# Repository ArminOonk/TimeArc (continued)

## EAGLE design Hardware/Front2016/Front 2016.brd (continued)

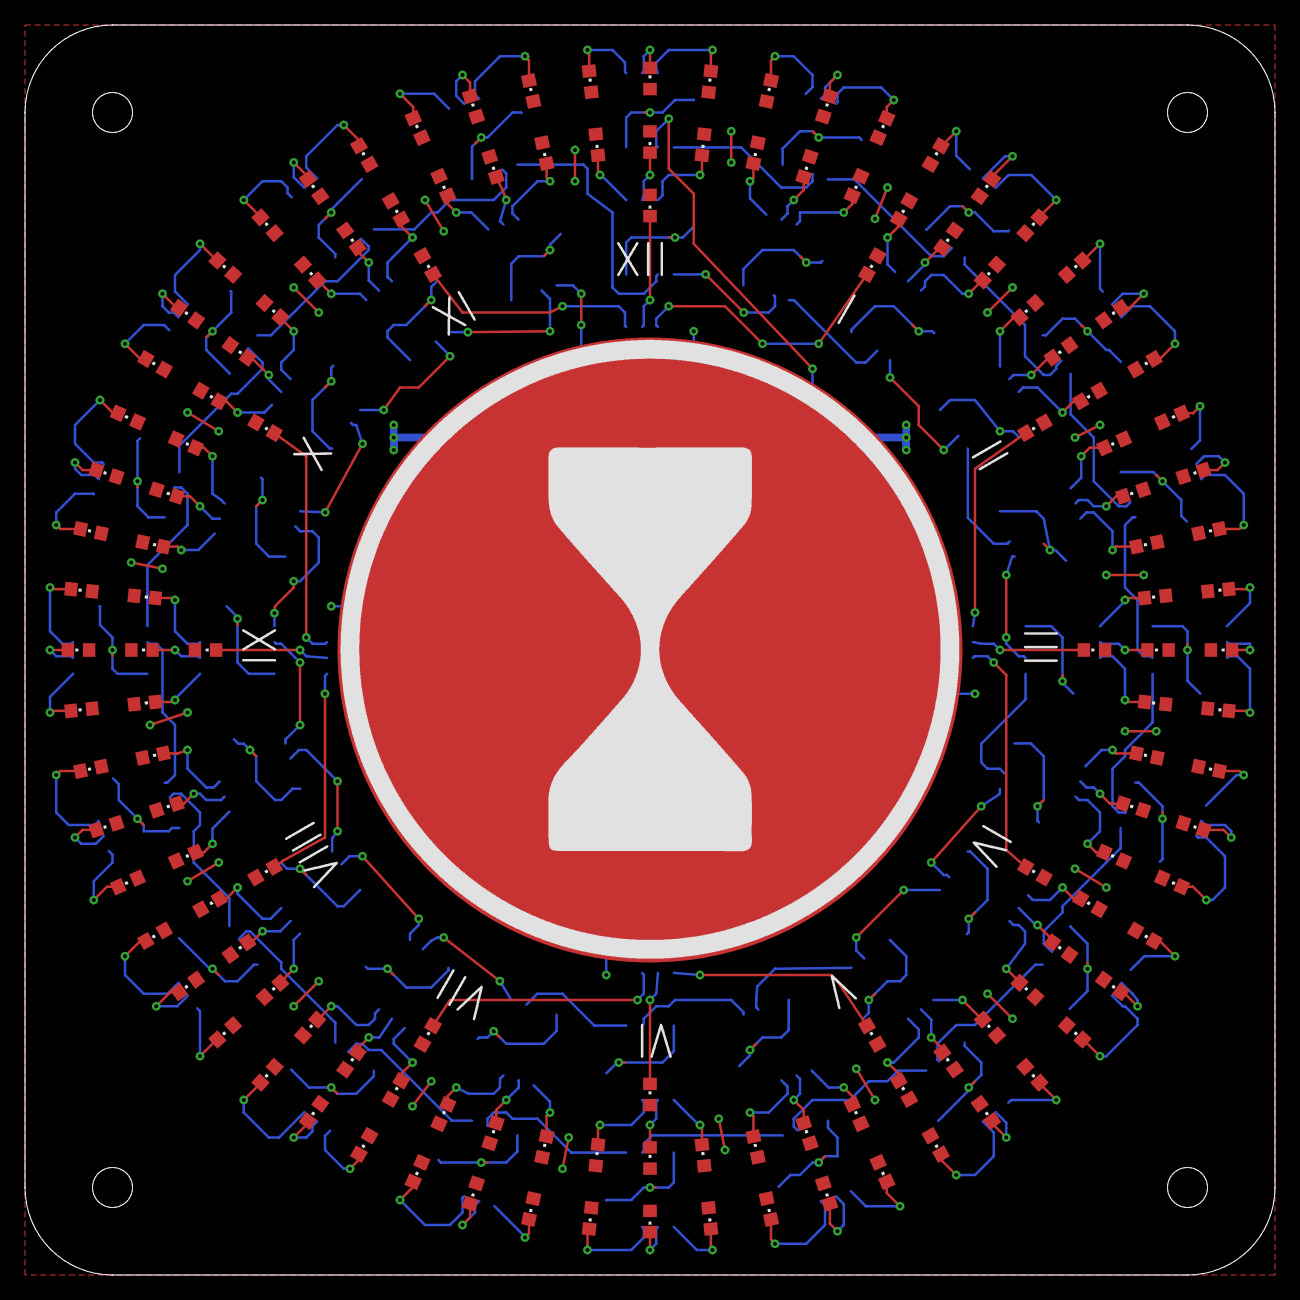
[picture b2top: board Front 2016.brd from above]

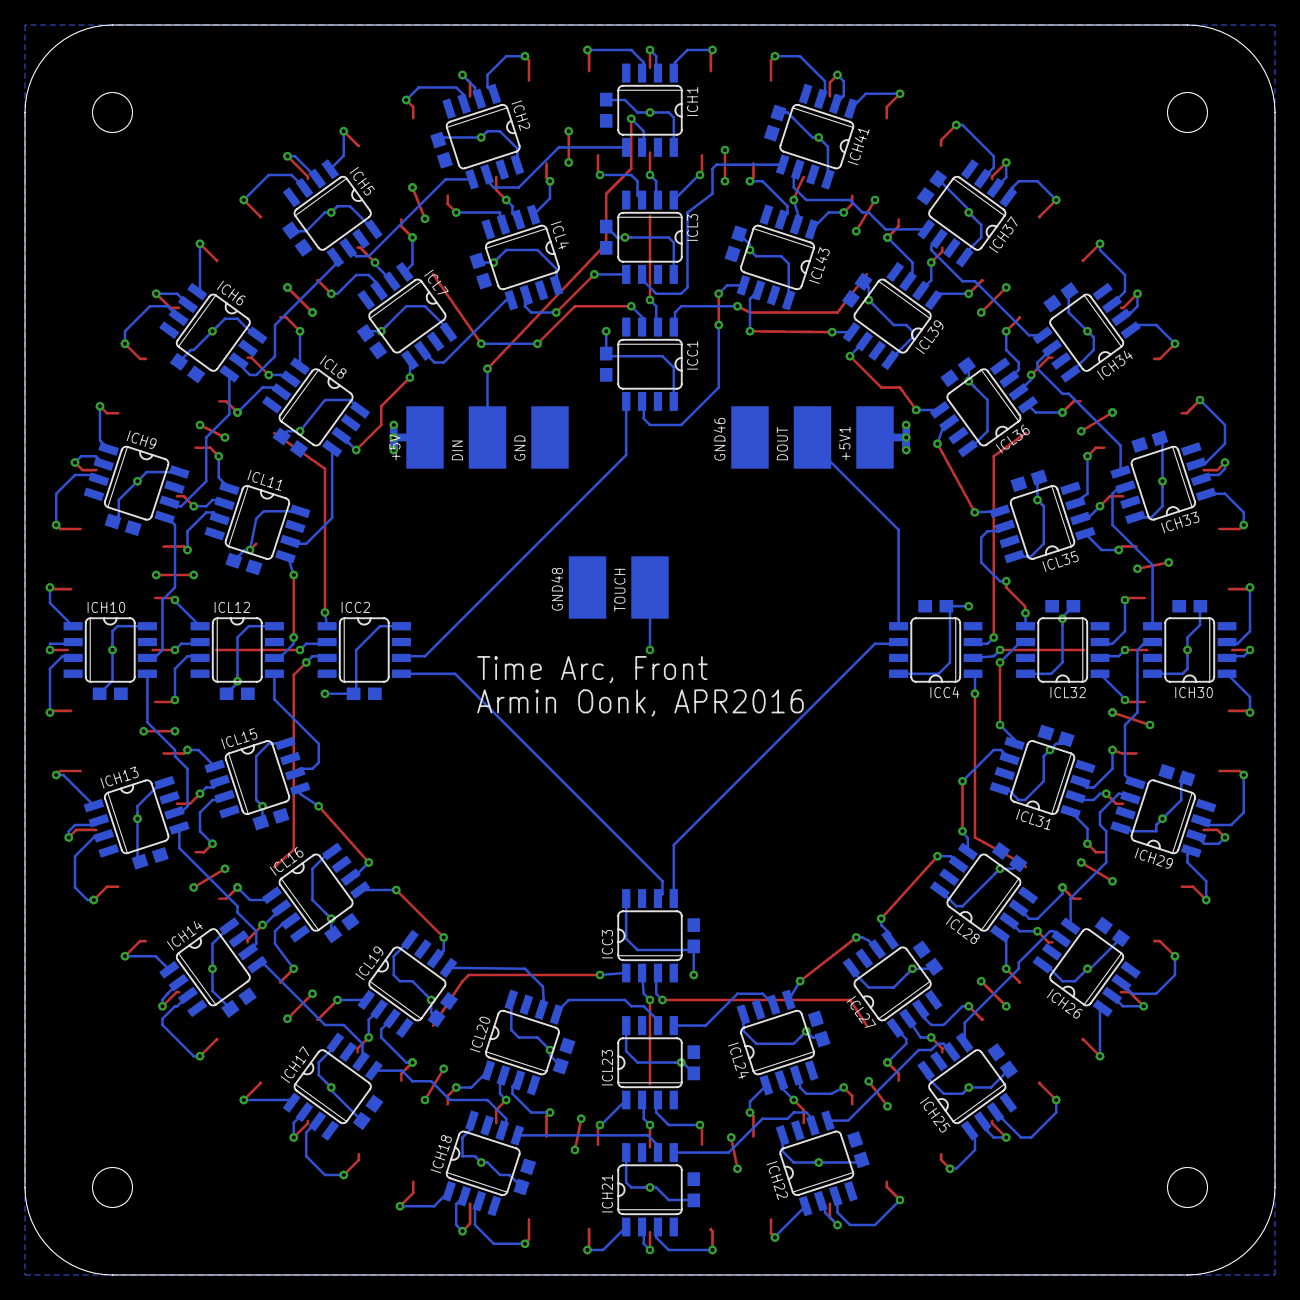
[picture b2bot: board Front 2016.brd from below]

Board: 2 copper layers, 100.0 x 100.0 mm, 187 parts (52 on the bottom side), 180 nets.

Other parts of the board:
U$1: TIMEARC_KEEPOUT
U$3: TIMEARC_LOGO_SIMPLE

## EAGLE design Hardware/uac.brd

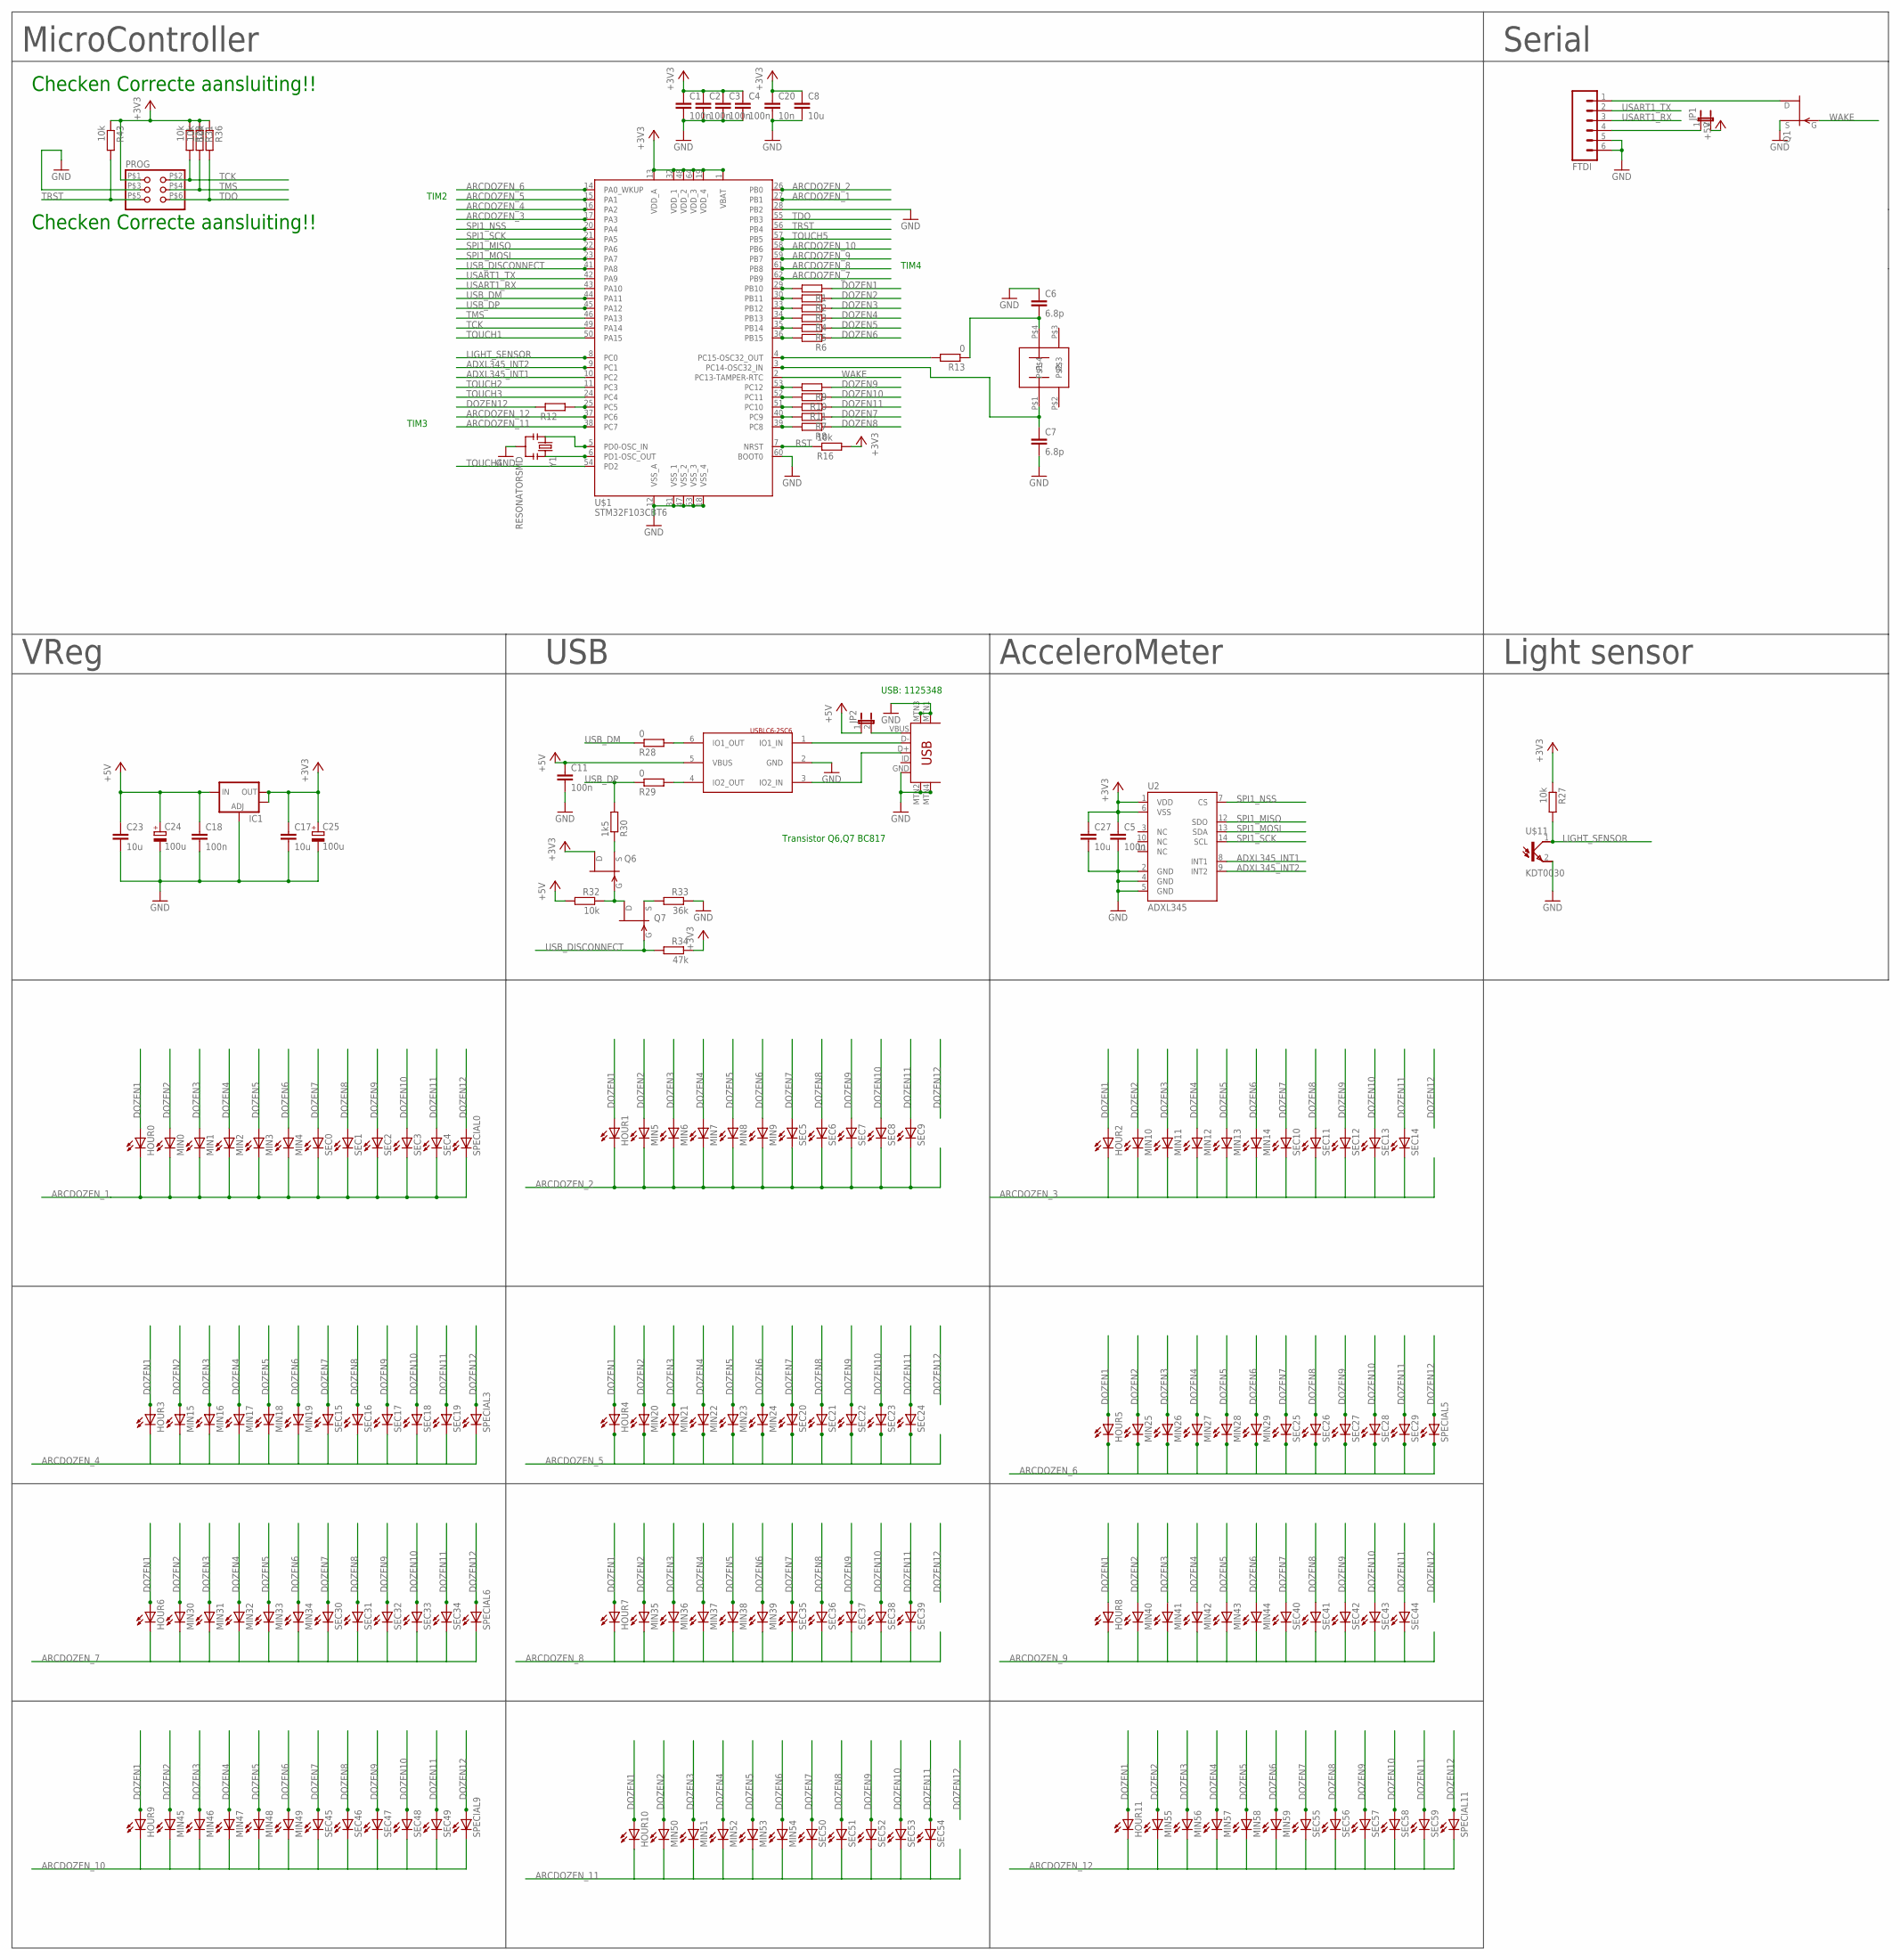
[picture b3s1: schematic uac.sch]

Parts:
C1, C2, C3, C4, C5, C11, C18: 100n; C0603
C6, C7: 6.8p; C0603
C8, C17, C23, C27: 10u; C0603
C20: 10n; C0603
C24, C25: 100u; SMC_C
FTDI: M06SMD; 1X06-SMD
HOUR0, HOUR1, HOUR2, HOUR3, HOUR4, HOUR5, HOUR6, HOUR7, HOUR8, HOUR9, HOUR10, HOUR11: LEDCHIPLED_0603; CHIPLED_0603
IC1: V_REG_LM1117SOT223; SOT223
JP1, JP2: JUMPER-2SMD-NO; SJ_2S-NO
MIN0, MIN1, MIN2, MIN3, MIN4, MIN5, MIN6, MIN7, MIN8, MIN9, MIN10, MIN11, MIN12, MIN13, MIN14, MIN15, MIN16, MIN17, MIN18, MIN19, MIN20, MIN21, MIN22, MIN23, MIN24, MIN25, MIN26, MIN27, MIN28, MIN29, MIN30, MIN31, MIN32, MIN33, MIN34, MIN35, MIN36, MIN37, MIN38, MIN39, MIN40, MIN41, MIN42, MIN43, MIN44, MIN45, MIN46, MIN47, MIN48, MIN49, MIN50, MIN51, MIN52, MIN53, MIN54, MIN55, MIN56, MIN57, MIN58, MIN59: LEDCHIPLED_0603; CHIPLED_0603
PROG: PINHD-2X3SMT; 2X03_SMT
Q1, Q6, Q7: 2N7002CK4SST; SOT23
R1, R2, R3, R4, R5, R6, R7, R8, R9, R10, R11, R12: R-EU_R0603; R0603
R13, R28, R29: 0; R0603
R16, R23, R27, R31, R32, R36, R43: 10k; R0603
R30: 1k5; R0603
R33: 36k; R0603
R34: 47k; R0603
SEC0, SEC1, SEC2, SEC3, SEC4, SEC5, SEC6, SEC7, SEC8, SEC9, SEC10, SEC11, SEC12, SEC13, SEC14, SEC15, SEC16, SEC17, SEC18, SEC19, SEC20, SEC21, SEC22, SEC23, SEC24, SEC25, SEC26, SEC27, SEC28, SEC29, SEC30, SEC31, SEC32, SEC33, SEC34, SEC35, SEC36, SEC37, SEC38, SEC39, SEC40, SEC41, SEC42, SEC43, SEC44, SEC45, SEC46, SEC47, SEC48, SEC49, SEC50, SEC51, SEC52, SEC53, SEC54, SEC55, SEC56, SEC57, SEC58, SEC59: LEDCHIPLED_0603; CHIPLED_0603
SPECIAL0, SPECIAL3, SPECIAL5, SPECIAL6, SPECIAL9, SPECIAL11: LEDCHIPLED_0603; CHIPLED_0603
U2: ADXL345; LGA14
U$1: STM32F103CBT6; LQFP64
U$2: CRYSTAL_32KHZ
U$11: KDT0030; FLD00030
U$12: USB-MINIB-5PIN; USB-MINIB
U$13: USBLC6-2SC6; SOT23
Y1: RESONATORSMD; RESONATOR-SMD

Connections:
+3V3: C1.1, C2.1, C3.1, C4.1, C5.1, C8.1, C17.1, C20.1, C25.+, C27.1, IC1.2 (OUT), IC1.4 (OUT), PROG.P$1 (1), Q6.3 (D), R16.2, R23.1, R27.1, R31.1, R34.1, R36.1, R43.1, U2.1 (VDD), U2.6 (VSS), U$1.1 (VBAT), U$1.13 (VDD_A), U$1.19 (VDD_4), U$1.32 (VDD_1), U$1.48 (VDD_2), U$1.64 (VDD_3)
+5V: C11.1, C18.1, C23.1, C24.+, IC1.3 (IN), JP1.2, JP2.1, R32.2, U$13.5 (VBUS)
ADXL345_INT1: U2.8 (INT1), U$1.10 (PC2)
ADXL345_INT2: U2.9 (INT2), U$1.9 (PC1)
ARCDOZEN_1: HOUR0.C, MIN0.C, MIN1.C, MIN2.C, MIN3.C, MIN4.C, SEC0.C, SEC1.C, SEC2.C, SEC3.C, SEC4.C, SPECIAL0.C, U$1.27 (PB1)
ARCDOZEN_2: HOUR1.C, MIN5.C, MIN6.C, MIN7.C, MIN8.C, MIN9.C, SEC5.C, SEC6.C, SEC7.C, SEC8.C, SEC9.C, U$1.26 (PB0)
ARCDOZEN_3: HOUR2.C, MIN10.C, MIN11.C, MIN12.C, MIN13.C, MIN14.C, SEC10.C, SEC11.C, SEC12.C, SEC13.C, SEC14.C, U$1.17 (PA3)
ARCDOZEN_4: HOUR3.C, MIN15.C, MIN16.C, MIN17.C, MIN18.C, MIN19.C, SEC15.C, SEC16.C, SEC17.C, SEC18.C, SEC19.C, SPECIAL3.C, U$1.16 (PA2)
ARCDOZEN_5: HOUR4.C, MIN20.C, MIN21.C, MIN22.C, MIN23.C, MIN24.C, SEC20.C, SEC21.C, SEC22.C, SEC23.C, SEC24.C, U$1.15 (PA1)
ARCDOZEN_6: HOUR5.C, MIN25.C, MIN26.C, MIN27.C, MIN28.C, MIN29.C, SEC25.C, SEC26.C, SEC27.C, SEC28.C, SEC29.C, SPECIAL5.C, U$1.14 (PA0_WKUP)
ARCDOZEN_7: HOUR6.C, MIN30.C, MIN31.C, MIN32.C, MIN33.C, MIN34.C, SEC30.C, SEC31.C, SEC32.C, SEC33.C, SEC34.C, SPECIAL6.C, U$1.62 (PB9)
ARCDOZEN_8: HOUR7.C, MIN35.C, MIN36.C, MIN37.C, MIN38.C, MIN39.C, SEC35.C, SEC36.C, SEC37.C, SEC38.C, SEC39.C, U$1.61 (PB8)
ARCDOZEN_9: HOUR8.C, MIN40.C, MIN41.C, MIN42.C, MIN43.C, MIN44.C, SEC40.C, SEC41.C, SEC42.C, SEC43.C, SEC44.C, U$1.59 (PB7)
ARCDOZEN_10: HOUR9.C, MIN45.C, MIN46.C, MIN47.C, MIN48.C, MIN49.C, SEC45.C, SEC46.C, SEC47.C, SEC48.C, SEC49.C, SPECIAL9.C, U$1.58 (PB6)
ARCDOZEN_11: HOUR10.C, MIN50.C, MIN51.C, MIN52.C, MIN53.C, MIN54.C, SEC50.C, SEC51.C, SEC52.C, SEC53.C, SEC54.C, U$1.38 (PC7)
ARCDOZEN_12: HOUR11.C, MIN55.C, MIN56.C, MIN57.C, MIN58.C, MIN59.C, SEC55.C, SEC56.C, SEC57.C, SEC58.C, SEC59.C, SPECIAL11.C, U$1.37 (PC6)
DOZEN1: HOUR0.A, HOUR1.A, HOUR2.A, HOUR3.A, HOUR4.A, HOUR5.A, HOUR6.A, HOUR7.A, HOUR8.A, HOUR9.A, HOUR10.A, HOUR11.A, R1.1
DOZEN2: MIN0.A, MIN5.A, MIN10.A, MIN15.A, MIN20.A, MIN25.A, MIN30.A, MIN35.A, MIN40.A, MIN45.A, MIN50.A, MIN55.A, R2.1
DOZEN3: MIN1.A, MIN6.A, MIN11.A, MIN16.A, MIN21.A, MIN26.A, MIN31.A, MIN36.A, MIN41.A, MIN46.A, MIN51.A, MIN56.A, R3.1
DOZEN4: MIN2.A, MIN7.A, MIN12.A, MIN17.A, MIN22.A, MIN27.A, MIN32.A, MIN37.A, MIN42.A, MIN47.A, MIN52.A, MIN57.A, R4.1
DOZEN5: MIN3.A, MIN8.A, MIN13.A, MIN18.A, MIN23.A, MIN28.A, MIN33.A, MIN38.A, MIN43.A, MIN48.A, MIN53.A, MIN58.A, R5.1
DOZEN6: MIN4.A, MIN9.A, MIN14.A, MIN19.A, MIN24.A, MIN29.A, MIN34.A, MIN39.A, MIN44.A, MIN49.A, MIN54.A, MIN59.A, R6.1
DOZEN7: R7.1, SEC0.A, SEC5.A, SEC10.A, SEC15.A, SEC20.A, SEC25.A, SEC30.A, SEC35.A, SEC40.A, SEC45.A, SEC50.A, SEC55.A
DOZEN8: R8.1, SEC1.A, SEC6.A, SEC11.A, SEC16.A, SEC21.A, SEC26.A, SEC31.A, SEC36.A, SEC41.A, SEC46.A, SEC51.A, SEC56.A
DOZEN9: R9.1, SEC2.A, SEC7.A, SEC12.A, SEC17.A, SEC22.A, SEC27.A, SEC32.A, SEC37.A, SEC42.A, SEC47.A, SEC52.A, SEC57.A
DOZEN10: R10.1, SEC3.A, SEC8.A, SEC13.A, SEC18.A, SEC23.A, SEC28.A, SEC33.A, SEC38.A, SEC43.A, SEC48.A, SEC53.A, SEC58.A
DOZEN11: R11.1, SEC4.A, SEC9.A, SEC14.A, SEC19.A, SEC24.A, SEC29.A, SEC34.A, SEC39.A, SEC44.A, SEC49.A, SEC54.A, SEC59.A
DOZEN12: R12.1, SPECIAL0.A, SPECIAL3.A, SPECIAL5.A, SPECIAL6.A, SPECIAL9.A, SPECIAL11.A
GND: C1.2, C2.2, C3.2, C4.2, C5.2, C6.1, C7.2, C8.2, C11.2, C17.2, C18.2, C20.2, C23.2, C24.-, C25.-, C27.2, FTDI.5, FTDI.6, IC1.1 (ADJ), PROG.P$3 (3), Q1.2 (S), R33.1, U2.2 (GND), U2.4 (GND), U2.5 (GND), U$1.12 (VSS_A), U$1.18 (VSS_4), U$1.28 (PB2), U$1.31 (VSS_1), U$1.47 (VSS_2), U$1.60 (BOOT0), U$1.63 (VSS_3), U$11.2 (EMI), U$12.GND, U$12.MTN1 (MTN2), U$12.MTN2 (MTN3), U$12.MTN3 (MTN1), U$12.MTN4, U$13.2 (GND), Y1.2
LIGHT_SENSOR: R27.2, U$1.8 (PC0), U$11.1 (COL)
unnamed: U$1.6 (PD1-OSC_OUT), Y1.3
unnamed: U$1.5 (PD0-OSC_IN), Y1.1
unnamed: JP2.2, U$12.VBUS
unnamed: R13.2, U$1.4 (PC15-OSC32_OUT)
unnamed: C6.2, R13.1, U$2.P$4
unnamed: C7.1, U$1.3 (PC14-OSC32_IN), U$2.P$1
unnamed: R1.2, U$1.29 (PB10)
unnamed: R2.2, U$1.30 (PB11)
unnamed: R3.2, U$1.33 (PB12)
unnamed: R4.2, U$1.34 (PB13)
unnamed: R5.2, U$1.35 (PB14)
unnamed: R6.2, U$1.36 (PB15)
unnamed: R7.2, U$1.40 (PC9)
unnamed: R8.2, U$1.39 (PC8)
unnamed: R9.2, U$1.53 (PC12)
unnamed: R10.2, U$1.52 (PC11)
unnamed: R11.2, U$1.51 (PC10)
unnamed: U$12.D-, U$13.1 (IO1_IN)
unnamed: FTDI.4, JP1.1
unnamed: FTDI.1, Q1.3 (D)
unnamed: U$12.D+, U$13.3 (IO2_IN)
unnamed: R12.2, U$1.25 (PC5)
unnamed: R28.2, U$13.6 (IO1_OUT)
unnamed: R29.2, U$13.4 (IO2_OUT)
unnamed: Q6.2 (S), R30.1
unnamed: Q6.1 (G), Q7.3 (D), R32.1
unnamed: Q7.2 (S), R33.2
RST: R16.1, U$1.7 (NRST)
SPI1_MISO: U2.12 (SDO), U$1.22 (PA6)
SPI1_MOSI: U2.13 (SDA), U$1.23 (PA7)
SPI1_NSS: U2.7 (CS), U$1.20 (PA4)
SPI1_SCK: U2.14 (SCL), U$1.21 (PA5)
TCK: PROG.P$2 (2), R23.2, U$1.49 (PA14)
TDO: PROG.P$6 (6), R36.2, U$1.55 (PB3)
TMS: PROG.P$4 (4), R31.2, U$1.46 (PA13)
TOUCH1: U$1.50 (PA15)
TOUCH2: U$1.11 (PC3)
TOUCH3: U$1.24 (PC4)
TOUCH4: U$1.54 (PD2)
TOUCH5: U$1.57 (PB5)
TRST: PROG.P$5 (5), R43.2, U$1.56 (PB4)
USART1_RX: FTDI.3, U$1.43 (PA10)
USART1_TX: FTDI.2, U$1.42 (PA9)
USB_DISCONNECT: Q7.1 (G), R34.2, U$1.41 (PA8)
USB_DM: R28.1, U$1.44 (PA11)
USB_DP: R29.1, R30.2, U$1.45 (PA12)
WAKE: Q1.1 (G), U$1.2 (PC13-TAMPER-RTC)

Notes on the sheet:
Checken Correcte aansluiting!!
TIM2
TIM4
VReg
MicroController
AcceleroMeter
Light sensor
Serial
USB
USB: 1125348
Transistor Q6,Q7 BC817
TIM3

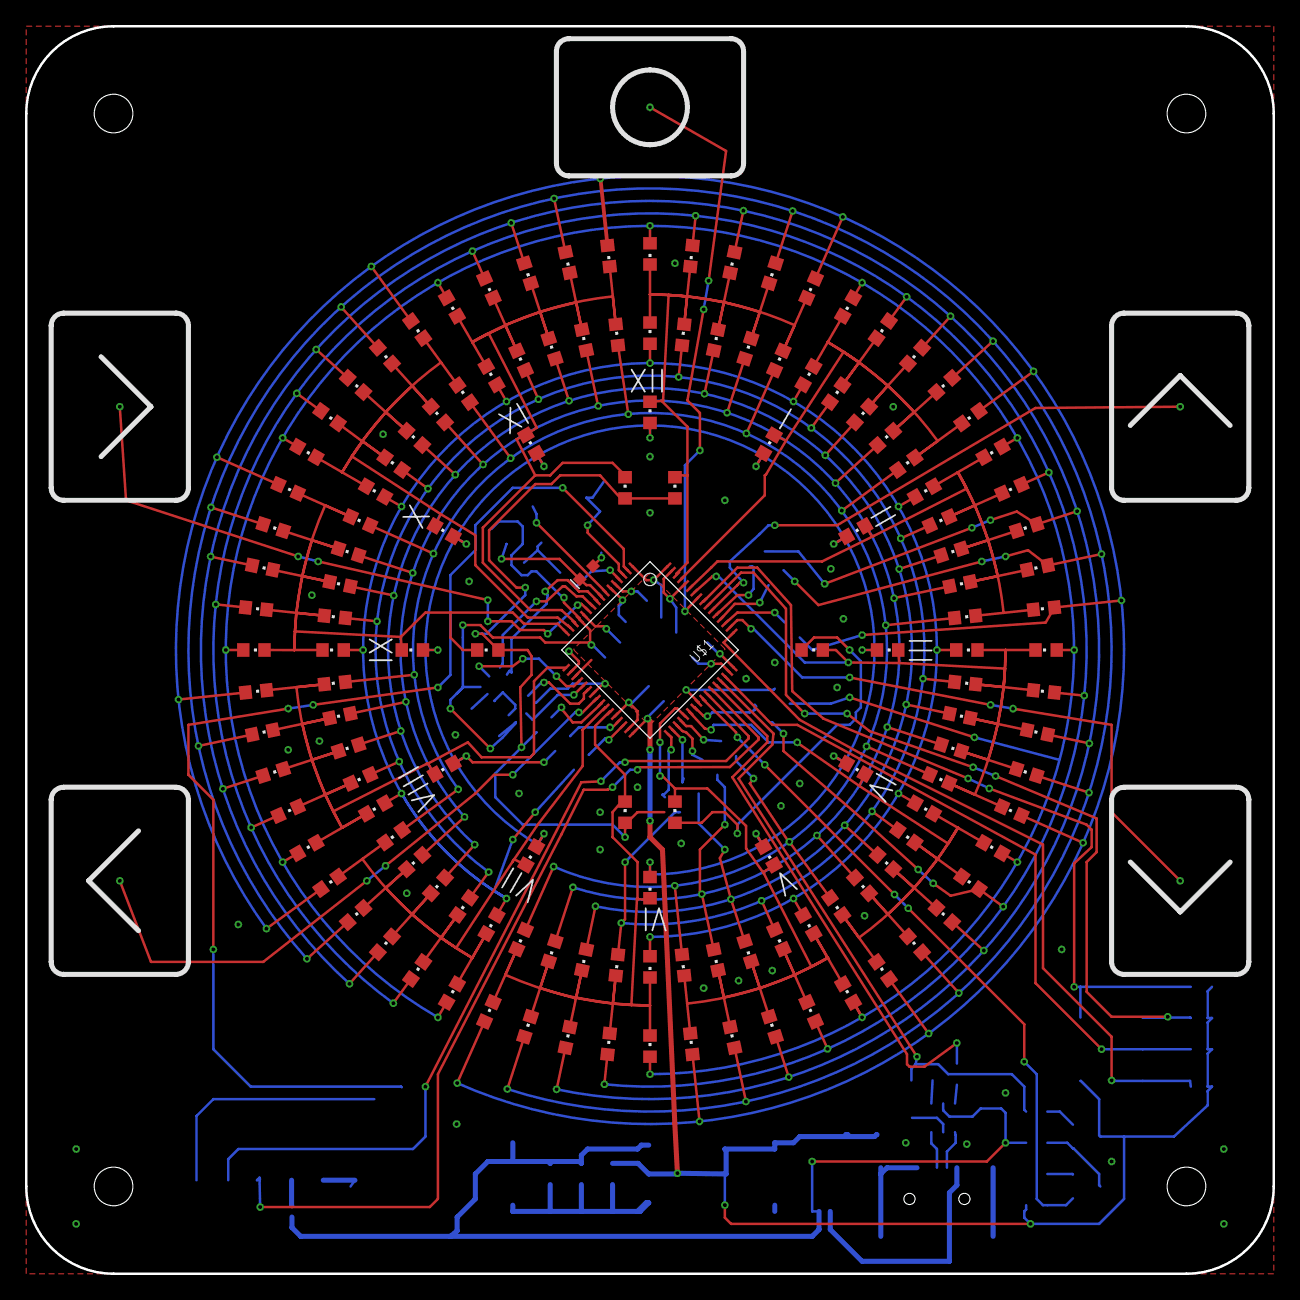
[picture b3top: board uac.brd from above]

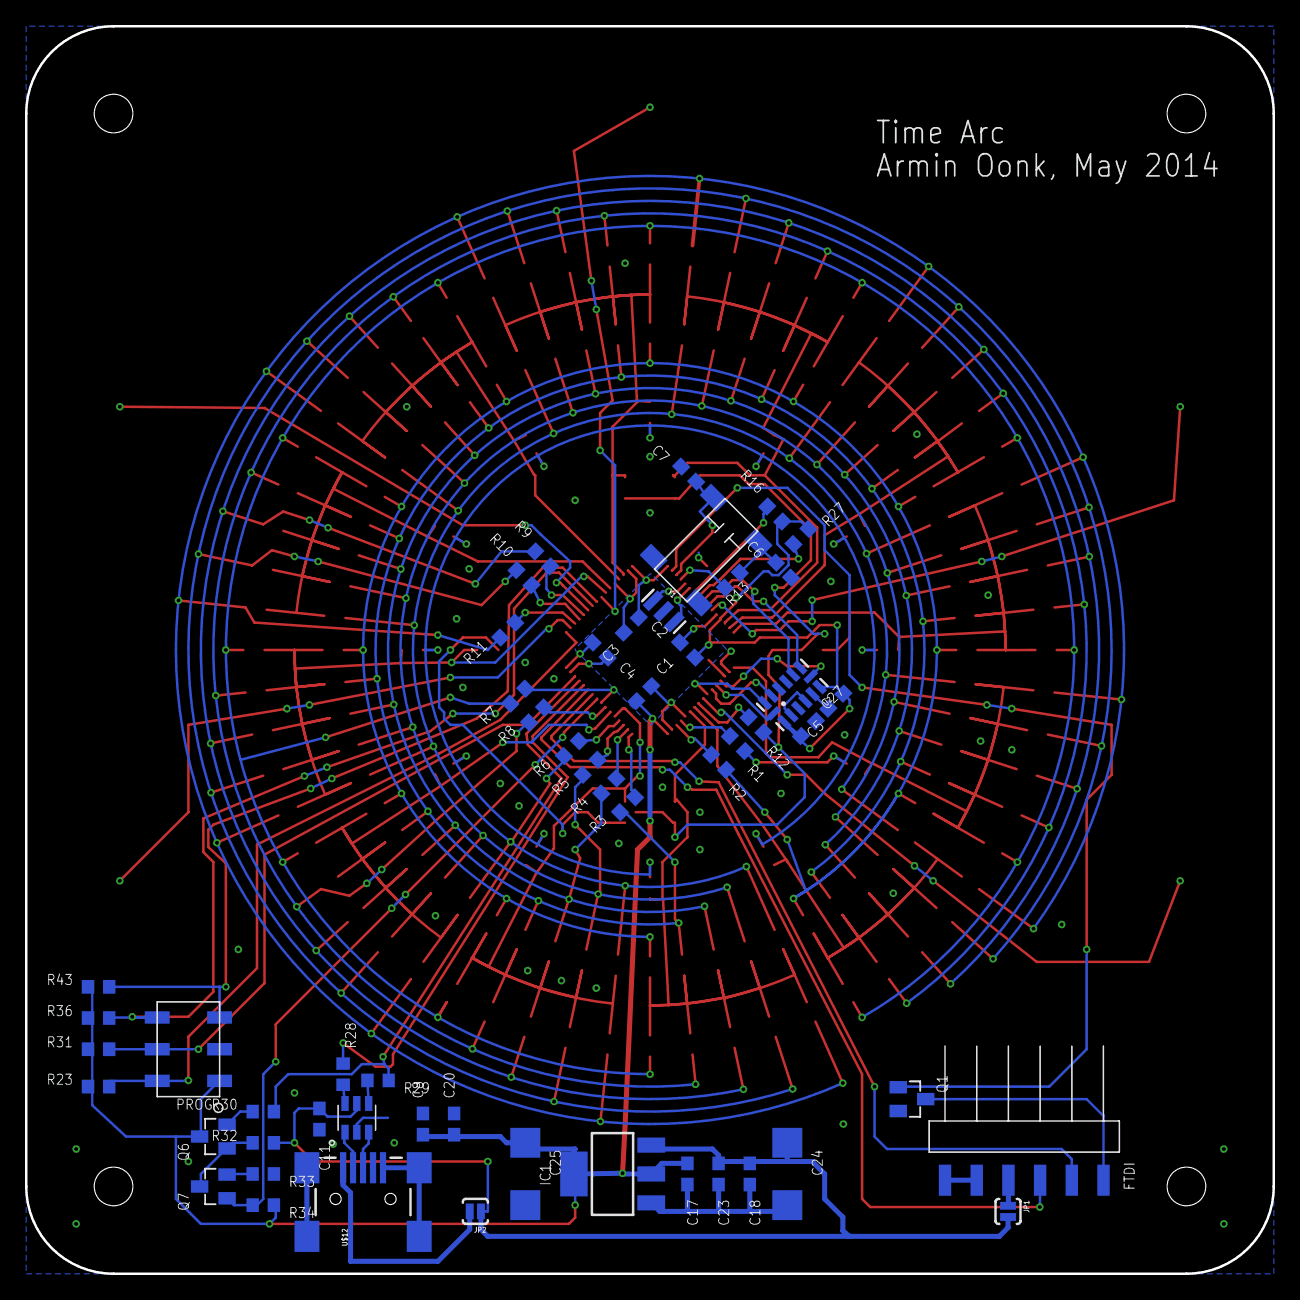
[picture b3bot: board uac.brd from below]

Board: 2 copper layers, 100.0 x 100.0 mm, 194 parts (54 on the bottom side), 72 nets.

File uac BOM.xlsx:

| Qty | Part | Value | Description | MPN | OC_DIGIKEY_1 | OC_FARNELL | U_PRICE_1 | Price total
 | 1 | C1 | 100n | CAPACITOR, European symbol |  |  | 1759016 | 7.0000000000000001E-3 | 7.0000000000000001E-3
 | 1 | C2 | 100n | CAPACITOR, European symbol |  |  | 1759016 | 7.0000000000000001E-3 | 7.0000000000000001E-3
 | 1 | C3 | 100n | CAPACITOR, European symbol |  |  | 1759016 | 7.0000000000000001E-3 | 7.0000000000000001E-3
 | 1 | C4 | 100n | CAPACITOR, European symbol |  |  | 1759016 | 7.0000000000000001E-3 | 7.0000000000000001E-3
 | 1 | C5 | 100n | CAPACITOR, European symbol |  |  | 1759016 | 7.0000000000000001E-3 | 7.0000000000000001E-3
 | 1 | C6 | 6.8p | CAPACITOR, European symbol |  |  | 1856099 | 0.03 | 0.03
 | 1 | C7 | 6.8p | CAPACITOR, European symbol |  |  | 1856099 | 0.03 | 0.03
 | 1 | C8 | 10u | CAPACITOR, European symbol |  |  | 1759393 | 0.12 | 0.12
 | 1 | C11 | 100n | CAPACITOR, European symbol |  |  | 1759016 | 7.0000000000000001E-3 | 7.0000000000000001E-3
 | 1 | C17 | 10u | CAPACITOR, European symbol |  |  | 1759393 | 0.12 | 0.12
 | 1 | C18 | 100n | CAPACITOR, European symbol |  |  | 1759016 | 7.0000000000000001E-3 | 7.0000000000000001E-3
 | 1 | C20 | 10n | CAPACITOR, European symbol |  |  | 1759102 | 7.0000000000000001E-3 | 7.0000000000000001E-3
 | 1 | C23 | 10u | CAPACITOR, European symbol |  |  | 1759393 | 0.12 | 0.12
 | 1 | C24 | 100u | POLARIZED CAPACITOR, European symbol |  |  | 1907361 | 1.84 | 1.84
 | 1 | C25 | 100u | POLARIZED CAPACITOR, European symbol |  |  | 1907361 | 1.84 | 1.84
 | 1 | C27 | 10u | CAPACITOR, European symbol |  |  | 1759393 | 0.12 | 0.12
 | 1 | FTDI |  | Header 6 |  |  | 2084270 | 1.22 | 1.22
 | 12 | HOUR0 |  | LED |  |  | 8529841 | 0.28000000000000003 | 3.3600000000000003
 | 1 | IC1 |  | Voltage Regulator LM1117 |  |  | 1469051 | 1.23 | 1.23
 | 60 | MIN0 |  | LED |  |  | 8529868 | 0.2 | 12
 | 1 | PROG |  | PIN HEADER |  |  | 2056005 | 0.45 | 0.45
 | 1 | Q1 | 2N7002CK4SST | N-Channel JFETs |  |  | 1829183 | 0.37 | 0.37
 | 1 | Q6 | 2N7002CK4SST | N-Channel JFETs |  |  | 1798076 | 2.23E-2 | 2.23E-2
 | 1 | Q7 | 2N7002CK4SST | N-Channel JFETs |  |  | 1798076 | 2.23E-2 | 2.23E-2
 | 1 | R1 |  | RESISTOR, European symbol |  |  | 2073347 | 8.0000000000000002E-3 | 8.0000000000000002E-3
 | 1 | R2 |  | RESISTOR, European symbol |  |  | 2073347 | 8.0000000000000002E-3 | 8.0000000000000002E-3
 | 1 | R3 |  | RESISTOR, European symbol |  |  | 2073347 | 8.0000000000000002E-3 | 8.0000000000000002E-3
 | 1 | R4 |  | RESISTOR, European symbol |  |  | 2073347 | 8.0000000000000002E-3 | 8.0000000000000002E-3
 | 1 | R5 |  | RESISTOR, European symbol |  |  | 2073347 | 8.0000000000000002E-3 | 8.0000000000000002E-3
 | 1 | R6 |  | RESISTOR, European symbol |  |  | 2073347 | 8.0000000000000002E-3 | 8.0000000000000002E-3
 | 1 | R7 |  | RESISTOR, European symbol |  |  | 2073347 | 8.0000000000000002E-3 | 8.0000000000000002E-3
 | 1 | R8 |  | RESISTOR, European symbol |  |  | 2073347 | 8.0000000000000002E-3 | 8.0000000000000002E-3
 | 1 | R9 |  | RESISTOR, European symbol |  |  | 2073347 | 8.0000000000000002E-3 | 8.0000000000000002E-3
 | 1 | R10 |  | RESISTOR, European symbol |  |  | 2073347 | 8.0000000000000002E-3 | 8.0000000000000002E-3
 | 1 | R11 |  | RESISTOR, European symbol |  |  | 2073347 | 8.0000000000000002E-3 | 8.0000000000000002E-3
 | 1 | R12 |  | RESISTOR, European symbol |  |  | 2073347 | 8.0000000000000002E-3 | 8.0000000000000002E-3
 | 1 | R13 | 0 | RESISTOR, European symbol |  |  | 2309106 | 4.7000000000000002E-3 | 4.7000000000000002E-3
 | 1 | R16 | 10k | RESISTOR, European symbol |  |  | 1469748 | 2.1000000000000001E-2 | 2.1000000000000001E-2
 | 1 | R23 | 10k | RESISTOR, European symbol |  |  | 1469748 | 2.1000000000000001E-2 | 2.1000000000000001E-2
 | 1 | R27 | 10k | RESISTOR, European symbol |  |  | 1469748 | 2.1000000000000001E-2 | 2.1000000000000001E-2
 | 1 | R28 | 0 | RESISTOR, European symbol |  |  | 2309106 | 4.7000000000000002E-3 | 4.7000000000000002E-3
 | 1 | R29 | 0 | RESISTOR, European symbol |  |  | 2309106 | 4.7000000000000002E-3 | 4.7000000000000002E-3
 | 1 | R30 | 1k5 | RESISTOR, European symbol |  |  | 2073391 | 8.0000000000000002E-3 | 8.0000000000000002E-3
 | 1 | R31 | 10k | RESISTOR, European symbol |  |  | 1469748 | 2.1000000000000001E-2 | 2.1000000000000001E-2
 | 1 | R32 | 10k | RESISTOR, European symbol |  |  | 1469748 | 2.1000000000000001E-2 | 2.1000000000000001E-2
 | 1 | R33 | 36k | RESISTOR, European symbol |  |  | 2138459 | 5.0000000000000001E-3 | 5.0000000000000001E-3
 | 1 | R34 | 47k | RESISTOR, European symbol |  |  | 2073515 | 8.0000000000000002E-3 | 8.0000000000000002E-3
 | 1 | R36 | 10k | RESISTOR, European symbol |  |  | 1469748 | 2.1000000000000001E-2 | 2.1000000000000001E-2
 | 1 | R43 | 10k | RESISTOR, European symbol |  |  | 1469748 | 2.1000000000000001E-2 | 2.1000000000000001E-2
 | 60 | SEC0 |  | LED |  |  | 2213649 | 0.19900000000000001 | 11.940000000000001
 | 60 |  |  |  |  |  | 2251459 | 9.1999999999999998E-2 | 5.52
 | 60 |  |  |  |  |  | 2217978 | 0.13400000000000001 | 8.0400000000000009
 | 1 | SPECIAL0 |  | LED |  |  |  |  | 0
 | 1 | SPECIAL3 |  | LED |  |  |  |  | 0
 | 1 | SPECIAL5 |  | LED |  |  |  |  | 0
 | 1 | SPECIAL6 |  | LED |  |  |  |  | 0
 | 1 | SPECIAL9 |  | LED |  |  |  |  | 0
 | 1 | SPECIAL11 |  | LED |  |  |  |  | 0
 | 1 | U$1 | STM32F103CBT6 |  |  |  | 1447640 | 5.71 | 5.71
 | 1 | U$2 | CRYSTAL_32KHZ |  | MC-306 32.768K-E3:ROHS | SER2417TR-ND |  |  | 0
 | 1 | U$11 | KDT0030 | Updated Light Sensor | KDT00030TR | KDT00030FSCT-ND |  | 0.6 | 0.6
 | 1 | U$12 | USB-MINIB-5PIN | Mini-USB B" connector with 5th pin broken out." |  |  | 1125348 | 0.56000000000000005 | 0.56000000000000005
 | 1 | U$13 | USBLC6-2SC6 |  | USBLC6-2SC6 |  | 1269406 | 0.76 | 0.76
 | 1 | U2 | ADXL345 |  |  |  | 1853935 | 5.38 | 5.38
 | 1 | Y1 | RESONATORSMD | Resonator |  | 490-1198-1-ND |  | 0.8 | 0.8
 |  |  |  |  |  |  |  | Total | 62.538699999999999

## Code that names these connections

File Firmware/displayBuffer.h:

#ifndef DISPLAY_BUFFER
#define DISPLAY_BUFFER
#include "stm32f10x.h"
#include "stm32f10x_conf.h"
#include "defines.h"
#include <string.h>
#include <time.h>
#include <stdio.h>

const int totalNrLeds = 144;
const int displayBufferSize = 144/8;

// DOZEN pins
#define DOZEN1_PORT   GPIOB
#define DOZEN1_PIN    GPIO_Pin_10
#define DOZEN1_LOW     DOZEN1_PORT->BRR |= DOZEN1_PIN
#define DOZEN1_HIGH    DOZEN1_PORT->BSRR |= DOZEN1_PIN

#define DOZEN2_PORT   GPIOB
#define DOZEN2_PIN    GPIO_Pin_11
#define DOZEN2_LOW     DOZEN2_PORT->BRR |= DOZEN2_PIN
#define DOZEN2_HIGH    DOZEN2_PORT->BSRR |= DOZEN2_PIN

#define DOZEN3_PORT   GPIOB
#define DOZEN3_PIN    GPIO_Pin_12
#define DOZEN3_LOW     DOZEN3_PORT->BRR |= DOZEN3_PIN
#define DOZEN3_HIGH    DOZEN3_PORT->BSRR |= DOZEN3_PIN

#define DOZEN4_PORT   GPIOB
#define DOZEN4_PIN    GPIO_Pin_13
#define DOZEN4_LOW     DOZEN4_PORT->BRR |= DOZEN4_PIN
#define DOZEN4_HIGH    DOZEN4_PORT->BSRR |= DOZEN4_PIN

#define DOZEN5_PORT   GPIOB
#define DOZEN5_PIN    GPIO_Pin_14
#define DOZEN5_LOW     DOZEN5_PORT->BRR |= DOZEN5_PIN
#define DOZEN5_HIGH    DOZEN5_PORT->BSRR |= DOZEN5_PIN

#define DOZEN6_PORT   GPIOB
#define DOZEN6_PIN    GPIO_Pin_15
#define DOZEN6_LOW     DOZEN6_PORT->BRR |= DOZEN6_PIN
#define DOZEN6_HIGH    DOZEN6_PORT->BSRR |= DOZEN6_PIN

#define DOZEN7_PORT   GPIOC
#define DOZEN7_PIN    GPIO_Pin_9
#define DOZEN7_LOW     DOZEN7_PORT->BRR |= DOZEN7_PIN
#define DOZEN7_HIGH    DOZEN7_PORT->BSRR |= DOZEN7_PIN

#define DOZEN8_PORT   GPIOC
#define DOZEN8_PIN    GPIO_Pin_8
#define DOZEN8_LOW     DOZEN8_PORT->BRR |= DOZEN8_PIN
#define DOZEN8_HIGH    DOZEN8_PORT->BSRR |= DOZEN8_PIN

#define DOZEN9_PORT   GPIOC
#define DOZEN9_PIN    GPIO_Pin_12
#define DOZEN9_LOW     DOZEN9_PORT->BRR |= DOZEN9_PIN
#define DOZEN9_HIGH    DOZEN9_PORT->BSRR |= DOZEN9_PIN

#define DOZEN10_PORT   GPIOC
#define DOZEN10_PIN    GPIO_Pin_11
#define DOZEN10_LOW     DOZEN10_PORT->BRR |= DOZEN10_PIN
#define DOZEN10_HIGH    DOZEN10_PORT->BSRR |= DOZEN10_PIN

#define DOZEN11_PORT   GPIOC
#define DOZEN11_PIN    GPIO_Pin_10
#define DOZEN11_LOW     DOZEN11_PORT->BRR |= DOZEN11_PIN
#define DOZEN11_HIGH    DOZEN11_PORT->BSRR |= DOZEN11_PIN

#define DOZEN12_PORT   GPIOC
#define DOZEN12_PIN    GPIO_Pin_5
#define DOZEN12_LOW     DOZEN12_PORT->BRR |= DOZEN12_PIN
#define DOZEN12_HIGH    DOZEN12_PORT->BSRR |= DOZEN12_PIN

// ARCDOZEN
#define ARCDOZEN1_PORT   GPIOB
#define ARCDOZEN1_PIN    GPIO_Pin_1
#define ARCDOZEN1_LOW     ARCDOZEN1_PORT->BRR |= ARCDOZEN1_PIN
#define ARCDOZEN1_HIGH    ARCDOZEN1_PORT->BSRR |= ARCDOZEN1_PIN

#define ARCDOZEN2_PORT   GPIOB
#define ARCDOZEN2_PIN    GPIO_Pin_0
#define ARCDOZEN2_LOW     ARCDOZEN2_PORT->BRR |= ARCDOZEN2_PIN
#define ARCDOZEN2_HIGH    ARCDOZEN2_PORT->BSRR |= ARCDOZEN2_PIN

#define ARCDOZEN3_PORT   GPIOA
#define ARCDOZEN3_PIN    GPIO_Pin_3
#define ARCDOZEN3_LOW     ARCDOZEN3_PORT->BRR |= ARCDOZEN3_PIN
#define ARCDOZEN3_HIGH    ARCDOZEN3_PORT->BSRR |= ARCDOZEN3_PIN

#define ARCDOZEN4_PORT   GPIOA
#define ARCDOZEN4_PIN    GPIO_Pin_2
#define ARCDOZEN4_LOW     ARCDOZEN4_PORT->BRR |= ARCDOZEN4_PIN
#define ARCDOZEN4_HIGH    ARCDOZEN4_PORT->BSRR |= ARCDOZEN4_PIN

#define ARCDOZEN5_PORT   GPIOA
#define ARCDOZEN5_PIN    GPIO_Pin_1
#define ARCDOZEN5_LOW     ARCDOZEN5_PORT->BRR |= ARCDOZEN5_PIN
#define ARCDOZEN5_HIGH    ARCDOZEN5_PORT->BSRR |= ARCDOZEN5_PIN

#define ARCDOZEN6_PORT   GPIOA
#define ARCDOZEN6_PIN    GPIO_Pin_0
#define ARCDOZEN6_LOW     ARCDOZEN6_PORT->BRR |= ARCDOZEN6_PIN
#define ARCDOZEN6_HIGH    ARCDOZEN6_PORT->BSRR |= ARCDOZEN6_PIN

#define ARCDOZEN7_PORT   GPIOB
#define ARCDOZEN7_PIN    GPIO_Pin_9
#define ARCDOZEN7_LOW     ARCDOZEN7_PORT->BRR |= ARCDOZEN7_PIN
#define ARCDOZEN7_HIGH    ARCDOZEN7_PORT->BSRR |= ARCDOZEN7_PIN

#define ARCDOZEN8_PORT   GPIOB
#define ARCDOZEN8_PIN    GPIO_Pin_8
#define ARCDOZEN8_LOW     ARCDOZEN8_PORT->BRR |= ARCDOZEN8_PIN
#define ARCDOZEN8_HIGH    ARCDOZEN8_PORT->BSRR |= ARCDOZEN8_PIN

#define ARCDOZEN9_PORT   GPIOB
#define ARCDOZEN9_PIN    GPIO_Pin_7
#define ARCDOZEN9_LOW     ARCDOZEN9_PORT->BRR |= ARCDOZEN9_PIN
#define ARCDOZEN9_HIGH    ARCDOZEN9_PORT->BSRR |= ARCDOZEN9_PIN

#define ARCDOZEN10_PORT   GPIOB
#define ARCDOZEN10_PIN    GPIO_Pin_6
#define ARCDOZEN10_LOW     ARCDOZEN10_PORT->BRR |= ARCDOZEN10_PIN
#define ARCDOZEN10_HIGH    ARCDOZEN10_PORT->BSRR |= ARCDOZEN10_PIN

#define ARCDOZEN11_PORT   GPIOC
#define ARCDOZEN11_PIN    GPIO_Pin_7
#define ARCDOZEN11_LOW     ARCDOZEN11_PORT->BRR |= ARCDOZEN11_PIN
#define ARCDOZEN11_HIGH    ARCDOZEN11_PORT->BSRR |= ARCDOZEN11_PIN

#define ARCDOZEN12_PORT   GPIOC
#define ARCDOZEN12_PIN    GPIO_Pin_6
#define ARCDOZEN12_LOW     ARCDOZEN12_PORT->BRR |= ARCDOZEN12_PIN
#define ARCDOZEN12_HIGH    ARCDOZEN12_PORT->BSRR |= ARCDOZEN12_PIN


enum clockIndex_t
{
  SECOND,
  MINUTE,
  HOUR,
};

class displayBuffer
{
  public:
  displayBuffer();

  void switchBuffer();
  void run();

  void ledOn(int ledNr);
  void ledOff(int ledNr);

  void setTime(time_t now);
  void hourOn(unsigned int hour);
  void minuteOn(unsigned int minute);
  void secondOn(unsigned int second);

  void setIntensity(float intensity);
  void displayOff();

  void setPose(pose_t p);
  void setMode(displayMode_t m);
  displayMode_t getMode();

  void printMode();

  private:
  void switchLedOn(int ledNr);
  
  void clearBuffer(int bufferNr);
  int nextBufferNr();
  
  bool isLedOn(int ledNr);
  char* getShowBuffer();
  char* getPaintBuffer();

  void animationMode();
  void clockMode();

  int getSecondLedNr(int second);
  int getMinuteLedNr(int minute);
  int getHourLedNr(int hour);

  int poseOffset(int org, int span);
  displayMode_t mode;
  pose_t pose;

  static const int nrBuffers = 2;
  int currentBuffer;
  char buffer[nrBuffers][displayBufferSize];
  int runCnt;

  int clockTime[3];
  int timerPeriod;

};

#endif
